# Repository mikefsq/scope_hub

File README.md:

# scope_hub

Telescope power and USB hub: six 12V/4A outputs, six 5 Gbit/s USB-C ports supplying 5V/2A, all ports support
switching, pwm control, and current monitoring. It also has a GPS, environment sensors and a Qwiic 
port. One of the six USB ports supports 5A to power a raspberry pi 5. Controled as a USB-HID device.

| Directory | Contents | License |
|---|---|---|
| `firmware` | RP2350 firmware | AGPL-3.0 |
| `driver` | Go driver and `scopehub` command | AGPL-3.0 |
| `pcb` | KiCad project | CERN-OHL-S-2.0 |
| `mech` | enclosure STEP files | CERN-OHL-S-2.0 |

See also the Alpaca switch driver is `scopehub` in [goalpaca-devices](https://github.com/mikefsq/goalpaca-devices).

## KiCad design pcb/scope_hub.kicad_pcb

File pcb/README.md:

# Scope Hub PCB

KiCad 10 project for the Scope Hub board: an RP2350A controller with six
switched 12 V outputs, six USB-C ports behind two TUSB hubs, per-port current
monitors, a GPS receiver and environment sensors.

- `scope_hub.kicad_pro` opens the project. `scope_hub.kicad_sch` is the root
  schematic; the other `.kicad_sch` files are its sheets.
- `scope_hub.kicad_pcb` is the layout, with custom rules in `scope_hub.kicad_dru`.
- `scope_hub.kicad_sym`, `scope_hub.pretty` and `scope_hub.3dshapes` hold the
  project's own symbols, footprints and 3D models. The library tables point at
  them relative to the project, so the folder opens as is on another machine.
- `fabrication-toolkit-options.json` configures the Fabrication Toolkit plugin,
  which writes the JLCPCB Gerbers, BOM and placement files.

The firmware is in `../firmware` and the host driver in `../driver`.

## License

Copyright (c) 2026 mikefsq

This source describes Open Hardware and is licensed under the CERN-OHL-S v2.
You may redistribute and modify this source and make products using it under
the terms of the [CERN-OHL-S v2](LICENSE). This source is distributed WITHOUT
ANY EXPRESS OR IMPLIED WARRANTY, INCLUDING OF MERCHANTABILITY, SATISFACTORY
QUALITY AND FITNESS FOR A PARTICULAR PURPOSE. Please see the CERN-OHL-S v2
for applicable conditions.

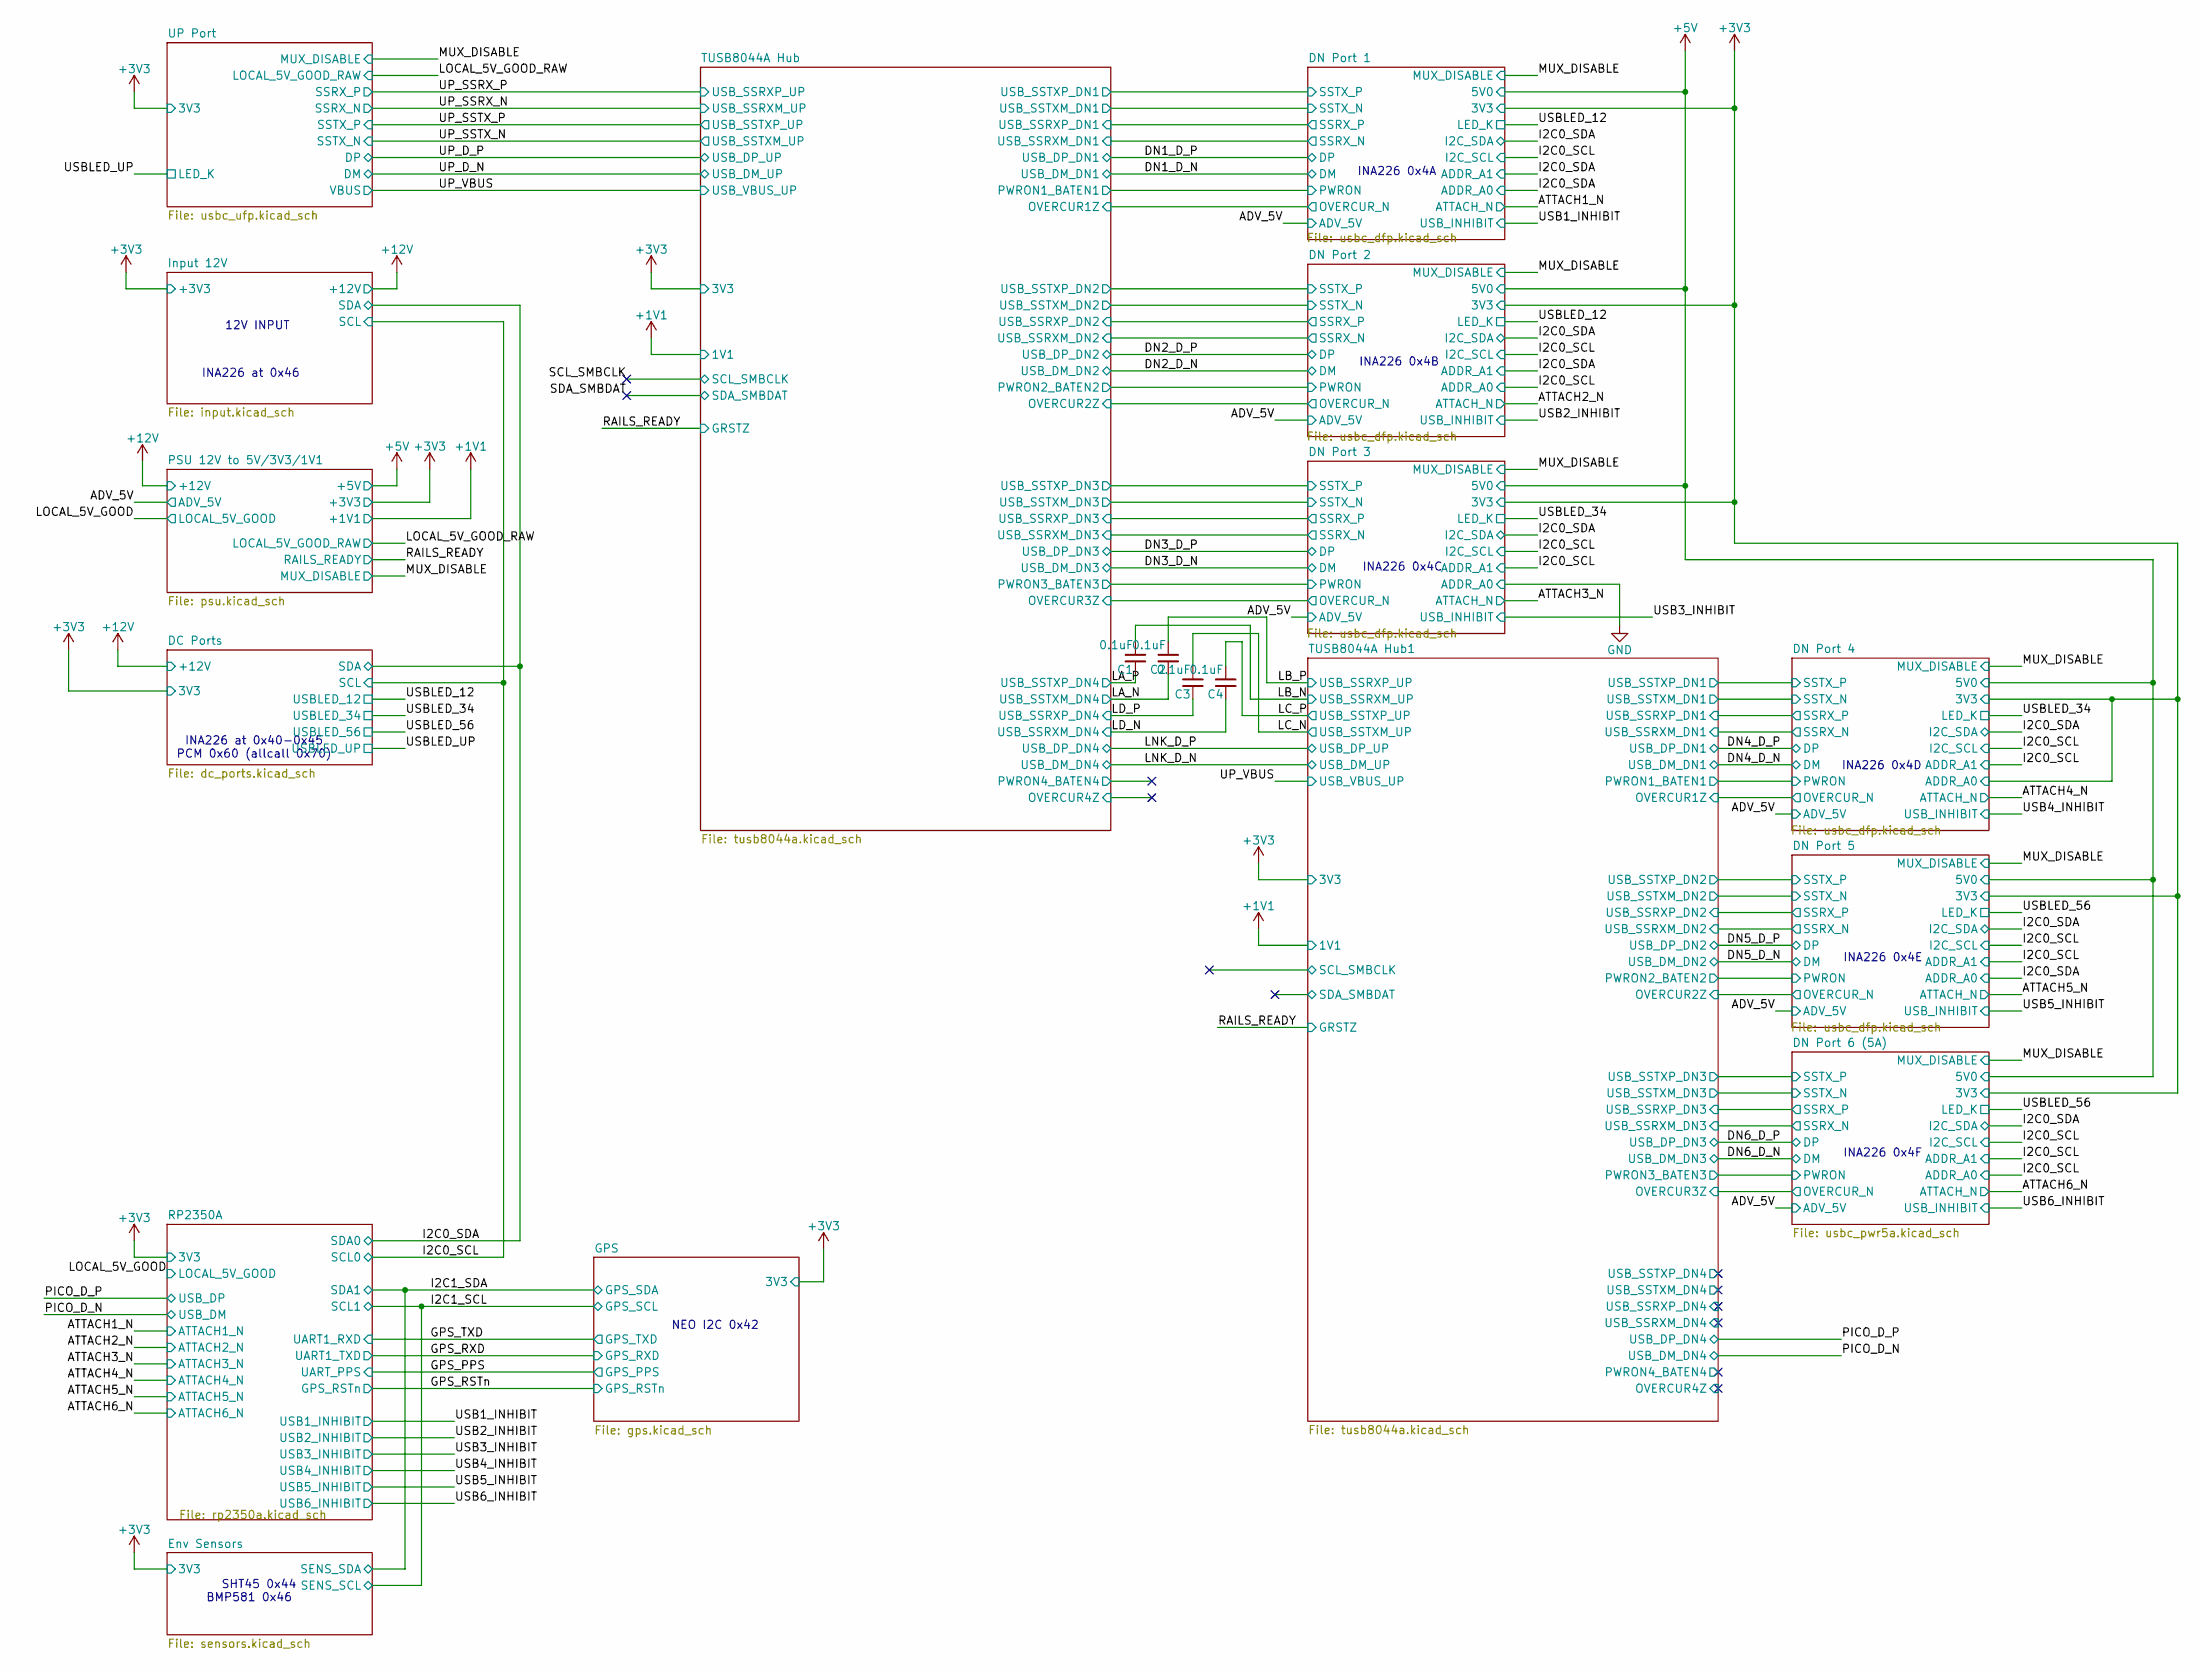
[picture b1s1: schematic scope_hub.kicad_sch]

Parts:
C1, C2, C3, C4: 0.1uF; C_0402_1005Metric; LCSC C1525

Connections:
/LA_N: C2.1; also elsewhere on the board
/LA_P: C1.1; also elsewhere on the board
/LB_N: C1.2; also elsewhere on the board
/LB_P: C2.2; also elsewhere on the board
/LC_N: C3.2; also elsewhere on the board
/LC_P: C4.2; also elsewhere on the board
/LD_N: C4.1; also elsewhere on the board
/LD_P: C3.1; also elsewhere on the board

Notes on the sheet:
12V INPUT
INA226 0x4C
INA226 at 0x40-0x45 PCM 0x60 (allcall 0x70)
INA226 0x4E
INA226 0x4B
INA226 0x4F
INA226 at 0x46
SHT45 0x44
BMP581 0x46
NEO I2C 0x42
INA226 0x4D
INA226 0x4A

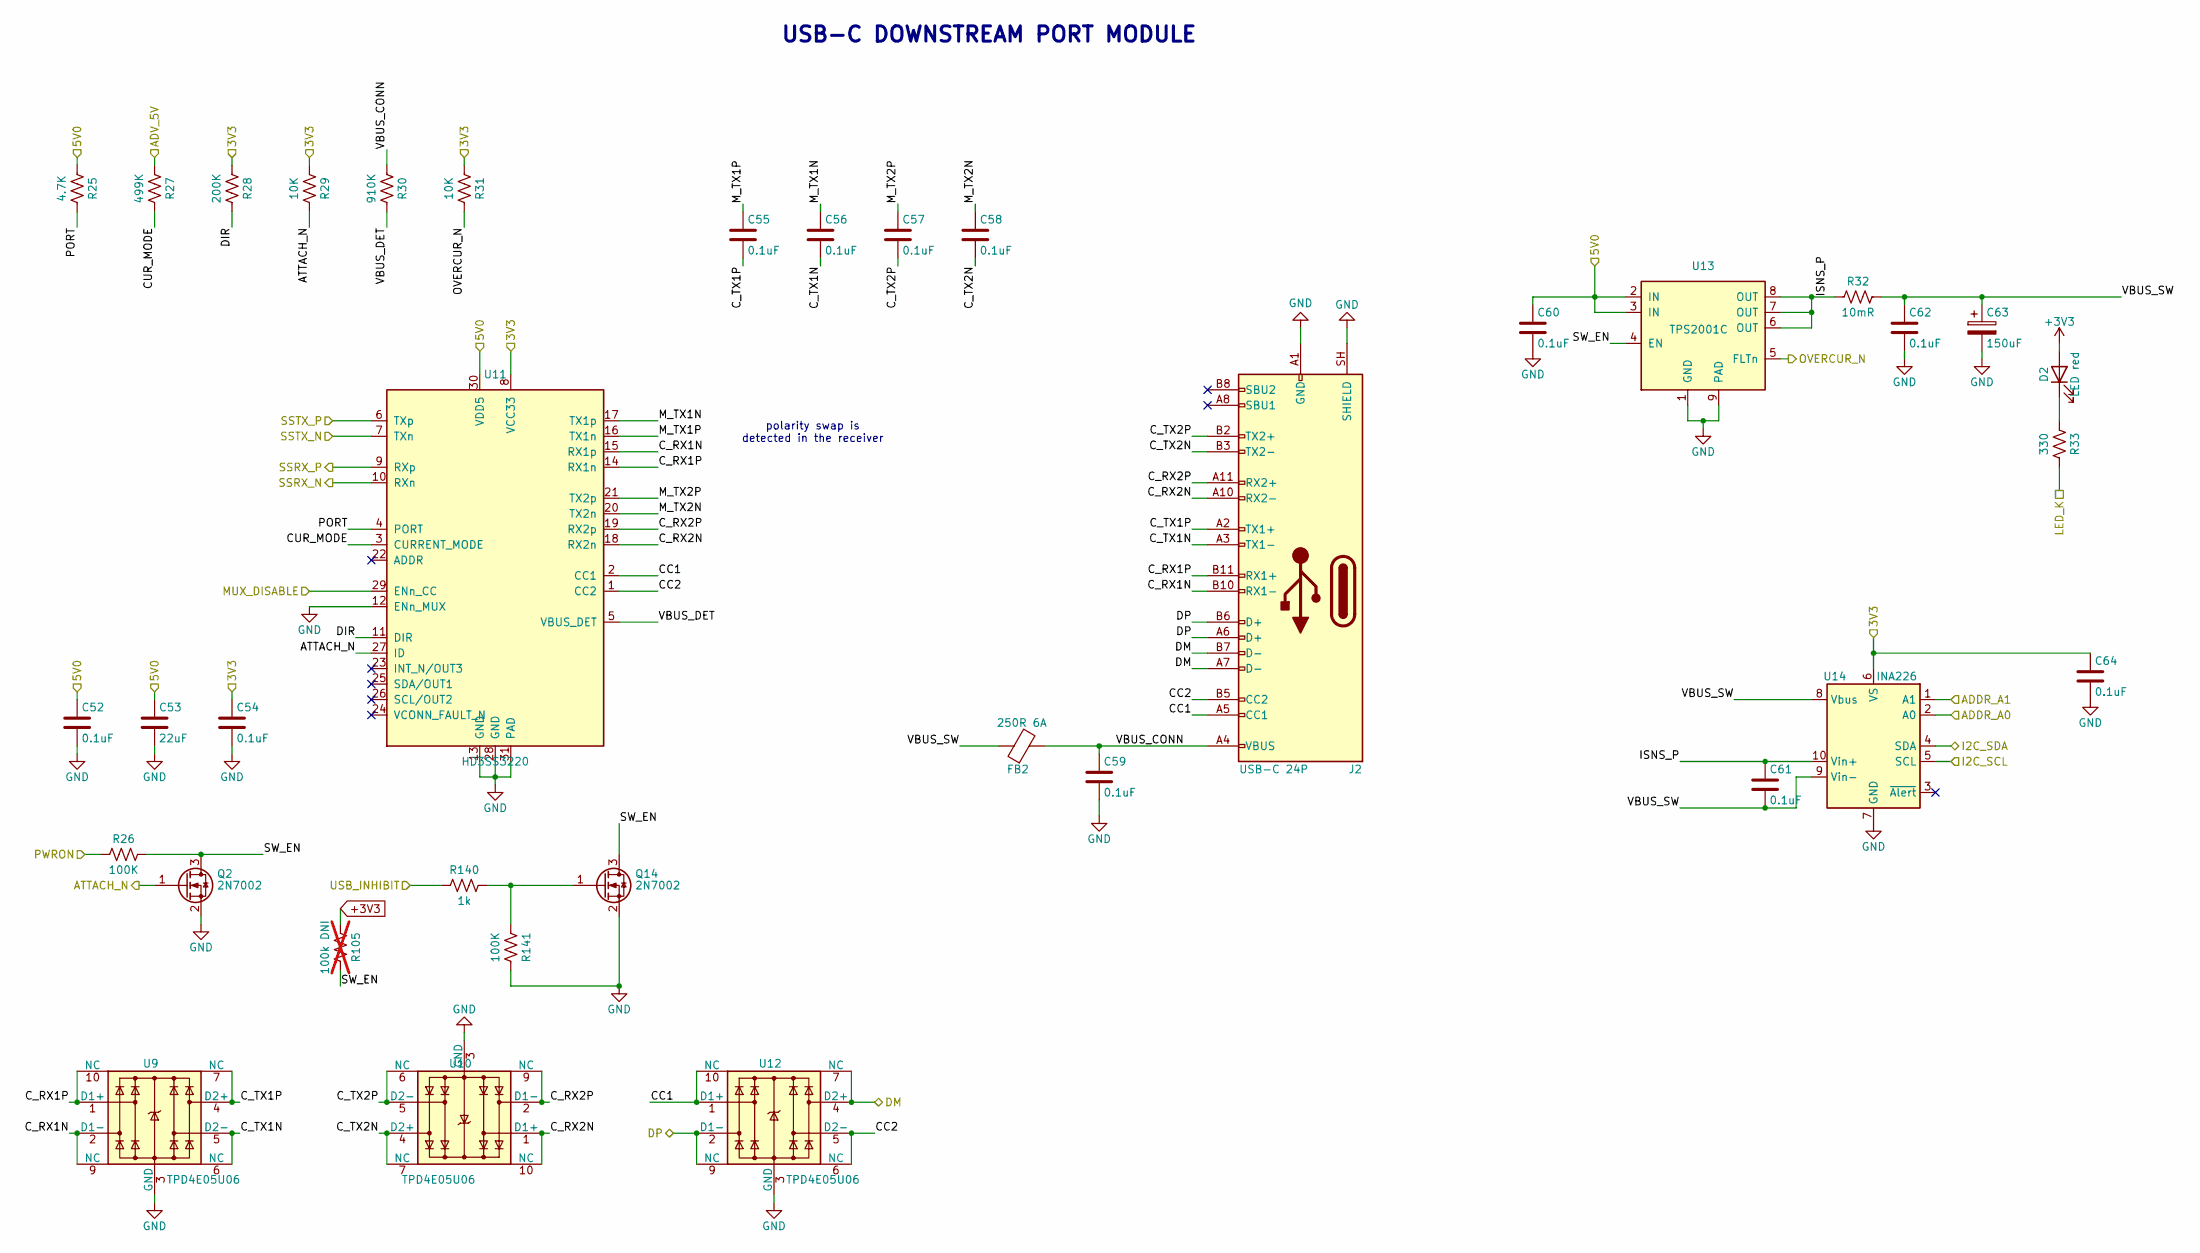
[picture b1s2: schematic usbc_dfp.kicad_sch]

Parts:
C52, C54, C55, C56, C57, C58, C59, C60, C61, C62, C64: 0.1uF; C_0402_1005Metric; LCSC C1525
C53: 22uF; C_0805_2012Metric; LCSC C45783
C63: 150uF; CP_EIA-3528-21_Kemet-B; LCSC C212682
D2: LED red; LED_0805_2012Metric; LCSC C84256
FB2: 250R 6A; FB_201210_PROD; MPN PSBHAA201210H-251T060; LCSC C48543401
J2: USB-C 24P; USB_C_Receptacle_Molex_105450-0101; MPN 105450-0101; LCSC C134092
Q2: 2N7002; SOT-23; LCSC C8545
Q14: 2N7002; SOT-23; MPN 2N7002; LCSC C8545
R25: 4.7K; R_0402_1005Metric; LCSC C25900
R26: 100K; R_0402_1005Metric; LCSC C25741
R27: 499K; R_0402_1005Metric; LCSC C25793
R28: 200K; R_0402_1005Metric; LCSC C25764
R29, R31: 10K; R_0402_1005Metric; LCSC C25744
R30: 910K; R_0402_1005Metric; LCSC C25800
R32: 10mR; R_1206_3216Metric; LCSC C105362
R33: 330; R_0402_1005Metric; LCSC C25104
R105: 100k DNI; R_0402_1005Metric; not fitted
R140: 1k; R_0402_1005Metric; MPN 0402WGF1001TCE; LCSC C11702
R141: 100K; R_0402_1005Metric; MPN 0402WGF1003TCE; LCSC C25741
U9, U10, U12: TPD4E05U06; USON-10_2.5x1.0mm_P0.5mm; LCSC C138714
U11: HD3SS3220; Texas_RNH0030A_WQFN-30-1EP_2.5x4.5mm_P0.4mm_EP1.2x3.2mm; LCSC C165155
U13: TPS2001C; MSOP-8-1EP_3x3mm_P0.65mm_EP1.68x1.88mm; LCSC C473349
U14: INA226; TSSOP-10_3x3mm_P0.5mm; LCSC C49851

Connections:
+3V3: C54.1, C64.1, D2.2 (A), R28.1, R29.1, R31.1, R105.1, U11.8 (VCC33), U14.6 (VS); also elsewhere on the board
+5V: C52.1, C53.1, C60.1, R25.1, U11.30 (VDD5), U13.2 (IN), U13.3 (IN); also elsewhere on the board
/ADV_5V: R27.1; also elsewhere on the board
/ATTACH2_N: Q2.1 (G), R29.2, U11.27 (ID); also elsewhere on the board
/DN2_D_N: J2.A7 (D-), J2.B7 (D-), U12.4 (D2+), U12.7 (NC); also elsewhere on the board
/DN2_D_P: J2.A6 (D+), J2.B6 (D+), U12.2 (D1-), U12.9 (NC); also elsewhere on the board
/DN Port 2/CC1: J2.A5 (CC1), U11.2 (CC1), U12.1 (D1+), U12.10 (NC)
/DN Port 2/CC2: J2.B5 (CC2), U11.1 (CC2), U12.5 (D2-), U12.6 (NC)
/DN Port 2/CUR_MODE: R27.2, U11.3 (CURRENT_MODE)
/DN Port 2/C_RX1N: J2.B10 (RX1-), U9.2 (D1-), U9.9 (NC), U11.15 (RX1p)
/DN Port 2/C_RX1P: J2.B11 (RX1+), U9.1 (D1+), U9.10 (NC), U11.14 (RX1n)
/DN Port 2/C_RX2N: J2.A10 (RX2-), U10.1 (D1+), U10.10 (NC), U11.18 (RX2n)
/DN Port 2/C_RX2P: J2.A11 (RX2+), U10.2 (D1-), U10.9 (NC), U11.19 (RX2p)
/DN Port 2/C_TX1N: C56.2, J2.A3 (TX1-), U9.5 (D2-), U9.6 (NC)
/DN Port 2/C_TX1P: C55.2, J2.A2 (TX1+), U9.4 (D2+), U9.7 (NC)
/DN Port 2/C_TX2N: C58.2, J2.B3 (TX2-), U10.4 (D2+), U10.7 (NC)
/DN Port 2/C_TX2P: C57.2, J2.B2 (TX2+), U10.5 (D2-), U10.6 (NC)
/DN Port 2/DIR: R28.2, U11.11 (DIR)
/DN Port 2/ISNS_P: C61.1, R32.1, U13.6 (OUT), U13.7 (OUT), U13.8 (OUT), U14.10 (Vin+)
/DN Port 2/M_TX1N: C56.1, U11.17 (TX1p)
/DN Port 2/M_TX1P: C55.1, U11.16 (TX1n)
/DN Port 2/M_TX2N: C58.1, U11.20 (TX2n)
/DN Port 2/M_TX2P: C57.1, U11.21 (TX2p)
/DN Port 2/OVERCUR_N: R31.2, U13.5 (FLTn); also elsewhere on the board
/DN Port 2/PORT: R25.2, U11.4 (PORT)
/DN Port 2/SSRX_N: U11.10 (RXn); also elsewhere on the board
/DN Port 2/SSRX_P: U11.9 (RXp); also elsewhere on the board
/DN Port 2/SSTX_N: U11.7 (TXn); also elsewhere on the board
/DN Port 2/SSTX_P: U11.6 (TXp); also elsewhere on the board
/DN Port 2/SW_EN: Q2.3 (D), Q14.3 (D), R26.2, R105.2, U13.4 (EN)
/DN Port 2/VBUS_CONN: C59.1, FB2.2, J2.A4 (VBUS), J2.A9 (VBUS), J2.B4 (VBUS), J2.B9 (VBUS), R30.1
/DN Port 2/VBUS_DET: R30.2, U11.5 (VBUS_DET)
/DN Port 2/VBUS_SW: C61.2, C62.1, C63.1, FB2.1, R32.2, U14.8 (Vbus), U14.9 (Vin-)
/I2C0_SCL: U14.2 (A0), U14.5 (SCL); also elsewhere on the board
/I2C0_SDA: U14.1 (A1), U14.4 (SDA); also elsewhere on the board
/MUX_DISABLE: U11.29 (ENn_CC); also elsewhere on the board
/TUSB8044A Hub/PWRON2_BATEN2: R26.1; also elsewhere on the board
/USB2_INHIBIT: R140.1; also elsewhere on the board
/USBLED_12: R33.2; also elsewhere on the board
GND: C52.2, C53.2, C54.2, C59.2, C60.2, C62.2, C63.2, C64.2, J2.A1 (GND), J2.A12 (GND), J2.B1 (GND), J2.B12 (GND), J2.SH (SHIELD), Q2.2 (S), Q14.2 (S), R141.2, U9.3 (GND), U9.8 (GND), U10.3 (GND), U10.8 (GND), U11.12 (ENn_MUX), U11.13 (GND), U11.28 (GND), U11.31 (PAD), U12.3 (GND), U12.8 (GND), U13.1 (GND), U13.9 (PAD), U14.7 (GND); also elsewhere on the board
unnamed: D2.1 (K), R33.1
unnamed: Q14.1 (G), R140.2, R141.1

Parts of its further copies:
C39, C41, C42, C43, C44, C45, C46, C47, C48, C49, C51, C65, C67, C68, C69, C70, C71, C72, C73, C74, C75, C77, C120, C122, C123, C124, C125, C126, C127, C128, C129, C130, C132, C133, C135, C136, C137, C138, C139, C140, C141, C142, C143, C145: 0.1uF; C_0402_1005Metric; LCSC C1525
C40, C66, C121, C134: 22uF; C_0805_2012Metric; LCSC C45783
C50, C76, C131, C144: 150uF; CP_EIA-3528-21_Kemet-B; LCSC C212682
D1, D3, D5, D6: LED red; LED_0805_2012Metric; LCSC C84256
FB1, FB3, FB5, FB6: 250R 6A; FB_201210_PROD; MPN PSBHAA201210H-251T060; LCSC C48543401
J1, J3, J5, J6: USB-C 24P; USB_C_Receptacle_Molex_105450-0101; MPN 105450-0101; LCSC C134092
Q1, Q3, Q4, Q5: 2N7002; SOT-23; LCSC C8545
Q8, Q9, Q10, Q11: 2N7002; SOT-23; MPN 2N7002; LCSC C8545
R16, R34, R62, R71: 4.7K; R_0402_1005Metric; LCSC C25900
R17, R35, R63, R72: 100K; R_0402_1005Metric; LCSC C25741
R18, R36, R64, R73: 499K; R_0402_1005Metric; LCSC C25793
R19, R37, R65, R74: 200K; R_0402_1005Metric; LCSC C25764
R20, R22, R38, R40, R66, R68, R75, R77: 10K; R_0402_1005Metric; LCSC C25744
R21, R39, R67, R76: 910K; R_0402_1005Metric; LCSC C25800
R23, R41, R69, R78: 10mR; R_1206_3216Metric; LCSC C105362
R24, R42, R70, R79: 330; R_0402_1005Metric; LCSC C25104
R142, R144, R146, R148: 1k; R_0402_1005Metric; MPN 0402WGF1001TCE; LCSC C11702
R143, R145, R147, R149: 100K; R_0402_1005Metric; MPN 0402WGF1003TCE; LCSC C25741
R167, R168, R169, R170: 100k DNI; R_0402_1005Metric; not fitted
U3, U4, U6, U15, U16, U18, U28, U29, U31, U34, U35, U37: TPD4E05U06; USON-10_2.5x1.0mm_P0.5mm; LCSC C138714
U5, U17, U30, U36: HD3SS3220; Texas_RNH0030A_WQFN-30-1EP_2.5x4.5mm_P0.4mm_EP1.2x3.2mm; LCSC C165155
U7, U19, U32, U38: TPS2001C; MSOP-8-1EP_3x3mm_P0.65mm_EP1.68x1.88mm; LCSC C473349
U8, U20, U33, U39: INA226; TSSOP-10_3x3mm_P0.5mm; LCSC C49851

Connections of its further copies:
+3V3: C41.1, C51.1, C67.1, C77.1, C122.1, C132.1, C135.1, C145.1, D1.2 (A), D3.2 (A), D5.2 (A), D6.2 (A), R19.1, R20.1, R22.1, R37.1, R38.1, R40.1, R65.1, R66.1, R68.1, R74.1, R75.1, R77.1, R167.1, R168.1, R169.1, R170.1, U5.8 (VCC33), U8.6 (VS), U17.8 (VCC33), U20.6 (VS), U30.8 (VCC33), U33.2 (A0), U33.6 (VS), U36.8 (VCC33), U39.6 (VS); also elsewhere on the board
+5V: C39.1, C40.1, C47.1, C65.1, C66.1, C73.1, C120.1, C121.1, C128.1, C133.1, C134.1, C141.1, R16.1, R34.1, R62.1, R71.1, U5.30 (VDD5), U7.2 (IN), U7.3 (IN), U17.30 (VDD5), U19.2 (IN), U19.3 (IN), U30.30 (VDD5), U32.2 (IN), U32.3 (IN), U36.30 (VDD5), U38.2 (IN), U38.3 (IN); also elsewhere on the board
/ADV_5V: R18.1, R36.1, R64.1, R73.1; also elsewhere on the board
/ATTACH1_N: Q1.1 (G), R20.2, U5.27 (ID); also elsewhere on the board
/ATTACH3_N: Q3.1 (G), R38.2, U17.27 (ID); also elsewhere on the board
/ATTACH4_N: Q4.1 (G), R66.2, U30.27 (ID); also elsewhere on the board
/ATTACH5_N: Q5.1 (G), R75.2, U36.27 (ID); also elsewhere on the board
/DN1_D_N: J1.A7 (D-), J1.B7 (D-), U6.4 (D2+), U6.7 (NC); also elsewhere on the board
/DN1_D_P: J1.A6 (D+), J1.B6 (D+), U6.2 (D1-), U6.9 (NC); also elsewhere on the board
/DN3_D_N: J3.A7 (D-), J3.B7 (D-), U18.4 (D2+), U18.7 (NC); also elsewhere on the board
/DN3_D_P: J3.A6 (D+), J3.B6 (D+), U18.2 (D1-), U18.9 (NC); also elsewhere on the board
/DN4_D_N: J5.A7 (D-), J5.B7 (D-), U31.4 (D2+), U31.7 (NC); also elsewhere on the board
/DN4_D_P: J5.A6 (D+), J5.B6 (D+), U31.2 (D1-), U31.9 (NC); also elsewhere on the board
/DN5_D_N: J6.A7 (D-), J6.B7 (D-), U37.4 (D2+), U37.7 (NC); also elsewhere on the board
/DN5_D_P: J6.A6 (D+), J6.B6 (D+), U37.2 (D1-), U37.9 (NC); also elsewhere on the board
/DN Port 1/CC1: J1.A5 (CC1), U5.2 (CC1), U6.1 (D1+), U6.10 (NC)
/DN Port 1/CC2: J1.B5 (CC2), U5.1 (CC2), U6.5 (D2-), U6.6 (NC)
/DN Port 1/CUR_MODE: R18.2, U5.3 (CURRENT_MODE)
/DN Port 1/C_RX1N: J1.B10 (RX1-), U3.2 (D1-), U3.9 (NC), U5.15 (RX1p)
/DN Port 1/C_RX1P: J1.B11 (RX1+), U3.1 (D1+), U3.10 (NC), U5.14 (RX1n)
/DN Port 1/C_RX2N: J1.A10 (RX2-), U4.1 (D1+), U4.10 (NC), U5.18 (RX2n)
/DN Port 1/C_RX2P: J1.A11 (RX2+), U4.2 (D1-), U4.9 (NC), U5.19 (RX2p)
/DN Port 1/C_TX1N: C43.2, J1.A3 (TX1-), U3.5 (D2-), U3.6 (NC)
/DN Port 1/C_TX1P: C42.2, J1.A2 (TX1+), U3.4 (D2+), U3.7 (NC)
/DN Port 1/C_TX2N: C45.2, J1.B3 (TX2-), U4.4 (D2+), U4.7 (NC)
/DN Port 1/C_TX2P: C44.2, J1.B2 (TX2+), U4.5 (D2-), U4.6 (NC)
/DN Port 1/DIR: R19.2, U5.11 (DIR)
/DN Port 1/ISNS_P: C48.1, R23.1, U7.6 (OUT), U7.7 (OUT), U7.8 (OUT), U8.10 (Vin+)
/DN Port 1/M_TX1N: C43.1, U5.17 (TX1p)
/DN Port 1/M_TX1P: C42.1, U5.16 (TX1n)
/DN Port 1/M_TX2N: C45.1, U5.20 (TX2n)
/DN Port 1/M_TX2P: C44.1, U5.21 (TX2p)
/DN Port 1/OVERCUR_N: R22.2, U7.5 (FLTn); also elsewhere on the board
/DN Port 1/PORT: R16.2, U5.4 (PORT)
/DN Port 1/SSRX_N: U5.10 (RXn); also elsewhere on the board
/DN Port 1/SSRX_P: U5.9 (RXp); also elsewhere on the board
/DN Port 1/SSTX_N: U5.7 (TXn); also elsewhere on the board
/DN Port 1/SSTX_P: U5.6 (TXp); also elsewhere on the board
/DN Port 1/SW_EN: Q1.3 (D), Q10.3 (D), R17.2, R169.2, U7.4 (EN)
/DN Port 1/VBUS_CONN: C46.1, FB1.2, J1.A4 (VBUS), J1.A9 (VBUS), J1.B4 (VBUS), J1.B9 (VBUS), R21.1
/DN Port 1/VBUS_DET: R21.2, U5.5 (VBUS_DET)
/DN Port 1/VBUS_SW: C48.2, C49.1, C50.1, FB1.1, R23.2, U8.8 (Vbus), U8.9 (Vin-)
/DN Port 3/CC1: J3.A5 (CC1), U17.2 (CC1), U18.1 (D1+), U18.10 (NC)
/DN Port 3/CC2: J3.B5 (CC2), U17.1 (CC2), U18.5 (D2-), U18.6 (NC)
/DN Port 3/CUR_MODE: R36.2, U17.3 (CURRENT_MODE)
/DN Port 3/C_RX1N: J3.B10 (RX1-), U15.2 (D1-), U15.9 (NC), U17.15 (RX1p)
/DN Port 3/C_RX1P: J3.B11 (RX1+), U15.1 (D1+), U15.10 (NC), U17.14 (RX1n)
/DN Port 3/C_RX2N: J3.A10 (RX2-), U16.1 (D1+), U16.10 (NC), U17.18 (RX2n)
/DN Port 3/C_RX2P: J3.A11 (RX2+), U16.2 (D1-), U16.9 (NC), U17.19 (RX2p)
/DN Port 3/C_TX1N: C69.2, J3.A3 (TX1-), U15.5 (D2-), U15.6 (NC)
/DN Port 3/C_TX1P: C68.2, J3.A2 (TX1+), U15.4 (D2+), U15.7 (NC)
/DN Port 3/C_TX2N: C71.2, J3.B3 (TX2-), U16.4 (D2+), U16.7 (NC)
/DN Port 3/C_TX2P: C70.2, J3.B2 (TX2+), U16.5 (D2-), U16.6 (NC)
/DN Port 3/DIR: R37.2, U17.11 (DIR)
/DN Port 3/ISNS_P: C74.1, R41.1, U19.6 (OUT), U19.7 (OUT), U19.8 (OUT), U20.10 (Vin+)
/DN Port 3/M_TX1N: C69.1, U17.17 (TX1p)
/DN Port 3/M_TX1P: C68.1, U17.16 (TX1n)
/DN Port 3/M_TX2N: C71.1, U17.20 (TX2n)
/DN Port 3/M_TX2P: C70.1, U17.21 (TX2p)
/DN Port 3/OVERCUR_N: R40.2, U19.5 (FLTn); also elsewhere on the board
/DN Port 3/PORT: R34.2, U17.4 (PORT)
/DN Port 3/SSRX_N: U17.10 (RXn); also elsewhere on the board
/DN Port 3/SSRX_P: U17.9 (RXp); also elsewhere on the board
/DN Port 3/SSTX_N: U17.7 (TXn); also elsewhere on the board
/DN Port 3/SSTX_P: U17.6 (TXp); also elsewhere on the board
/DN Port 3/SW_EN: Q3.3 (D), Q8.3 (D), R35.2, R167.2, U19.4 (EN)
/DN Port 3/VBUS_CONN: C72.1, FB3.2, J3.A4 (VBUS), J3.A9 (VBUS), J3.B4 (VBUS), J3.B9 (VBUS), R39.1
/DN Port 3/VBUS_DET: R39.2, U17.5 (VBUS_DET)
/DN Port 3/VBUS_SW: C74.2, C75.1, C76.1, FB3.1, R41.2, U20.8 (Vbus), U20.9 (Vin-)
/DN Port 4/CC1: J5.A5 (CC1), U30.2 (CC1), U31.1 (D1+), U31.10 (NC)
/DN Port 4/CC2: J5.B5 (CC2), U30.1 (CC2), U31.5 (D2-), U31.6 (NC)
/DN Port 4/CUR_MODE: R64.2, U30.3 (CURRENT_MODE)
/DN Port 4/C_RX1N: J5.B10 (RX1-), U28.2 (D1-), U28.9 (NC), U30.15 (RX1p)
/DN Port 4/C_RX1P: J5.B11 (RX1+), U28.1 (D1+), U28.10 (NC), U30.14 (RX1n)
/DN Port 4/C_RX2N: J5.A10 (RX2-), U29.1 (D1+), U29.10 (NC), U30.18 (RX2n)
/DN Port 4/C_RX2P: J5.A11 (RX2+), U29.2 (D1-), U29.9 (NC), U30.19 (RX2p)
/DN Port 4/C_TX1N: C124.2, J5.A3 (TX1-), U28.5 (D2-), U28.6 (NC)
/DN Port 4/C_TX1P: C123.2, J5.A2 (TX1+), U28.4 (D2+), U28.7 (NC)
/DN Port 4/C_TX2N: C126.2, J5.B3 (TX2-), U29.4 (D2+), U29.7 (NC)
/DN Port 4/C_TX2P: C125.2, J5.B2 (TX2+), U29.5 (D2-), U29.6 (NC)
/DN Port 4/DIR: R65.2, U30.11 (DIR)
/DN Port 4/ISNS_P: C129.1, R69.1, U32.6 (OUT), U32.7 (OUT), U32.8 (OUT), U33.10 (Vin+)
/DN Port 4/M_TX1N: C124.1, U30.17 (TX1p)
/DN Port 4/M_TX1P: C123.1, U30.16 (TX1n)
/DN Port 4/M_TX2N: C126.1, U30.20 (TX2n)
/DN Port 4/M_TX2P: C125.1, U30.21 (TX2p)
/DN Port 4/OVERCUR_N: R68.2, U32.5 (FLTn); also elsewhere on the board
/DN Port 4/PORT: R62.2, U30.4 (PORT)
/DN Port 4/SSRX_N: U30.10 (RXn); also elsewhere on the board
/DN Port 4/SSRX_P: U30.9 (RXp); also elsewhere on the board
/DN Port 4/SSTX_N: U30.7 (TXn); also elsewhere on the board
/DN Port 4/SSTX_P: U30.6 (TXp); also elsewhere on the board
/DN Port 4/SW_EN: Q4.3 (D), Q9.3 (D), R63.2, R168.2, U32.4 (EN)
/DN Port 4/VBUS_CONN: C127.1, FB5.2, J5.A4 (VBUS), J5.A9 (VBUS), J5.B4 (VBUS), J5.B9 (VBUS), R67.1
/DN Port 4/VBUS_DET: R67.2, U30.5 (VBUS_DET)
/DN Port 4/VBUS_SW: C129.2, C130.1, C131.1, FB5.1, R69.2, U33.8 (Vbus), U33.9 (Vin-)
/DN Port 5/CC1: J6.A5 (CC1), U36.2 (CC1), U37.1 (D1+), U37.10 (NC)
/DN Port 5/CC2: J6.B5 (CC2), U36.1 (CC2), U37.5 (D2-), U37.6 (NC)
/DN Port 5/CUR_MODE: R73.2, U36.3 (CURRENT_MODE)
/DN Port 5/C_RX1N: J6.B10 (RX1-), U34.2 (D1-), U34.9 (NC), U36.15 (RX1p)
/DN Port 5/C_RX1P: J6.B11 (RX1+), U34.1 (D1+), U34.10 (NC), U36.14 (RX1n)
/DN Port 5/C_RX2N: J6.A10 (RX2-), U35.1 (D1+), U35.10 (NC), U36.18 (RX2n)
/DN Port 5/C_RX2P: J6.A11 (RX2+), U35.2 (D1-), U35.9 (NC), U36.19 (RX2p)
/DN Port 5/C_TX1N: C137.2, J6.A3 (TX1-), U34.5 (D2-), U34.6 (NC)
/DN Port 5/C_TX1P: C136.2, J6.A2 (TX1+), U34.4 (D2+), U34.7 (NC)
/DN Port 5/C_TX2N: C139.2, J6.B3 (TX2-), U35.4 (D2+), U35.7 (NC)
/DN Port 5/C_TX2P: C138.2, J6.B2 (TX2+), U35.5 (D2-), U35.6 (NC)
/DN Port 5/DIR: R74.2, U36.11 (DIR)
/DN Port 5/ISNS_P: C142.1, R78.1, U38.6 (OUT), U38.7 (OUT), U38.8 (OUT), U39.10 (Vin+)
/DN Port 5/M_TX1N: C137.1, U36.17 (TX1p)
/DN Port 5/M_TX1P: C136.1, U36.16 (TX1n)
/DN Port 5/M_TX2N: C139.1, U36.20 (TX2n)
/DN Port 5/M_TX2P: C138.1, U36.21 (TX2p)
/DN Port 5/OVERCUR_N: R77.2, U38.5 (FLTn); also elsewhere on the board
/DN Port 5/PORT: R71.2, U36.4 (PORT)
/DN Port 5/SSRX_N: U36.10 (RXn); also elsewhere on the board
/DN Port 5/SSRX_P: U36.9 (RXp); also elsewhere on the board
/DN Port 5/SSTX_N: U36.7 (TXn); also elsewhere on the board
/DN Port 5/SSTX_P: U36.6 (TXp); also elsewhere on the board
/DN Port 5/SW_EN: Q5.3 (D), Q11.3 (D), R72.2, R170.2, U38.4 (EN)
/DN Port 5/VBUS_CONN: C140.1, FB6.2, J6.A4 (VBUS), J6.A9 (VBUS), J6.B4 (VBUS), J6.B9 (VBUS), R76.1
/DN Port 5/VBUS_DET: R76.2, U36.5 (VBUS_DET)
/DN Port 5/VBUS_SW: C142.2, C143.1, C144.1, FB6.1, R78.2, U39.8 (Vbus), U39.9 (Vin-)
/I2C0_SCL: U8.5 (SCL), U20.1 (A1), U20.5 (SCL), U33.1 (A1), U33.5 (SCL), U39.1 (A1), U39.5 (SCL); also elsewhere on the board
/I2C0_SDA: U8.1 (A1), U8.2 (A0), U8.4 (SDA), U20.4 (SDA), U33.4 (SDA), U39.2 (A0), U39.4 (SDA); also elsewhere on the board
/MUX_DISABLE: U5.29 (ENn_CC), U17.29 (ENn_CC), U30.29 (ENn_CC), U36.29 (ENn_CC); also elsewhere on the board
/TUSB8044A Hub1/PWRON1_BATEN1: R63.1; also elsewhere on the board
/TUSB8044A Hub1/PWRON2_BATEN2: R72.1; also elsewhere on the board
/TUSB8044A Hub/PWRON1_BATEN1: R17.1; also elsewhere on the board
/TUSB8044A Hub/PWRON3_BATEN3: R35.1; also elsewhere on the board
/USB1_INHIBIT: R146.1; also elsewhere on the board
/USB3_INHIBIT: R142.1; also elsewhere on the board
/USB4_INHIBIT: R144.1; also elsewhere on the board
/USB5_INHIBIT: R148.1; also elsewhere on the board
/USBLED_12: R24.2; also elsewhere on the board
/USBLED_34: R42.2, R70.2; also elsewhere on the board
/USBLED_56: R79.2; also elsewhere on the board
GND: C39.2, C40.2, C41.2, C46.2, C47.2, C49.2, C50.2, C51.2, C65.2, C66.2, C67.2, C72.2, C73.2, C75.2, C76.2, C77.2, C120.2, C121.2, C122.2, C127.2, C128.2, C130.2, C131.2, C132.2, C133.2, C134.2, C135.2, C140.2, C141.2, C143.2, C144.2, C145.2, J1.A1 (GND), J1.A12 (GND), J1.B1 (GND), J1.B12 (GND), J1.SH (SHIELD), J3.A1 (GND), J3.A12 (GND), J3.B1 (GND), J3.B12 (GND), J3.SH (SHIELD), J5.A1 (GND), J5.A12 (GND), J5.B1 (GND), J5.B12 (GND), J5.SH (SHIELD), J6.A1 (GND), J6.A12 (GND), J6.B1 (GND), J6.B12 (GND), J6.SH (SHIELD), Q1.2 (S), Q3.2 (S), Q4.2 (S), Q5.2 (S), Q8.2 (S), Q9.2 (S), Q10.2 (S), Q11.2 (S), R143.2, R145.2, R147.2, R149.2, U3.3 (GND), U3.8 (GND), U4.3 (GND), U4.8 (GND), U5.12 (ENn_MUX), U5.13 (GND), U5.28 (GND), U5.31 (PAD), U6.3 (GND), U6.8 (GND), U7.1 (GND), U7.9 (PAD), U8.7 (GND), U15.3 (GND), U15.8 (GND), U16.3 (GND), U16.8 (GND), U17.12 (ENn_MUX), U17.13 (GND), U17.28 (GND), U17.31 (PAD), U18.3 (GND), U18.8 (GND), U19.1 (GND), U19.9 (PAD), U20.2 (A0), U20.7 (GND), U28.3 (GND), U28.8 (GND), U29.3 (GND), U29.8 (GND), U30.12 (ENn_MUX), U30.13 (GND), U30.28 (GND), U30.31 (PAD), U31.3 (GND), U31.8 (GND), U32.1 (GND), U32.9 (PAD), U33.7 (GND), U34.3 (GND), U34.8 (GND), U35.3 (GND), U35.8 (GND), U36.12 (ENn_MUX), U36.13 (GND), U36.28 (GND), U36.31 (PAD), U37.3 (GND), U37.8 (GND), U38.1 (GND), U38.9 (PAD), U39.7 (GND); also elsewhere on the board
unnamed: D1.1 (K), R24.1
unnamed: D3.1 (K), R42.1
unnamed: D5.1 (K), R70.1
unnamed: D6.1 (K), R79.1
unnamed: Q8.1 (G), R142.2, R143.1
unnamed: Q9.1 (G), R144.2, R145.1
unnamed: Q10.1 (G), R146.2, R147.1
unnamed: Q11.1 (G), R148.2, R149.1

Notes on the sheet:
USB-C DOWNSTREAM PORT MODULE
polarity swap is detected in the receiver

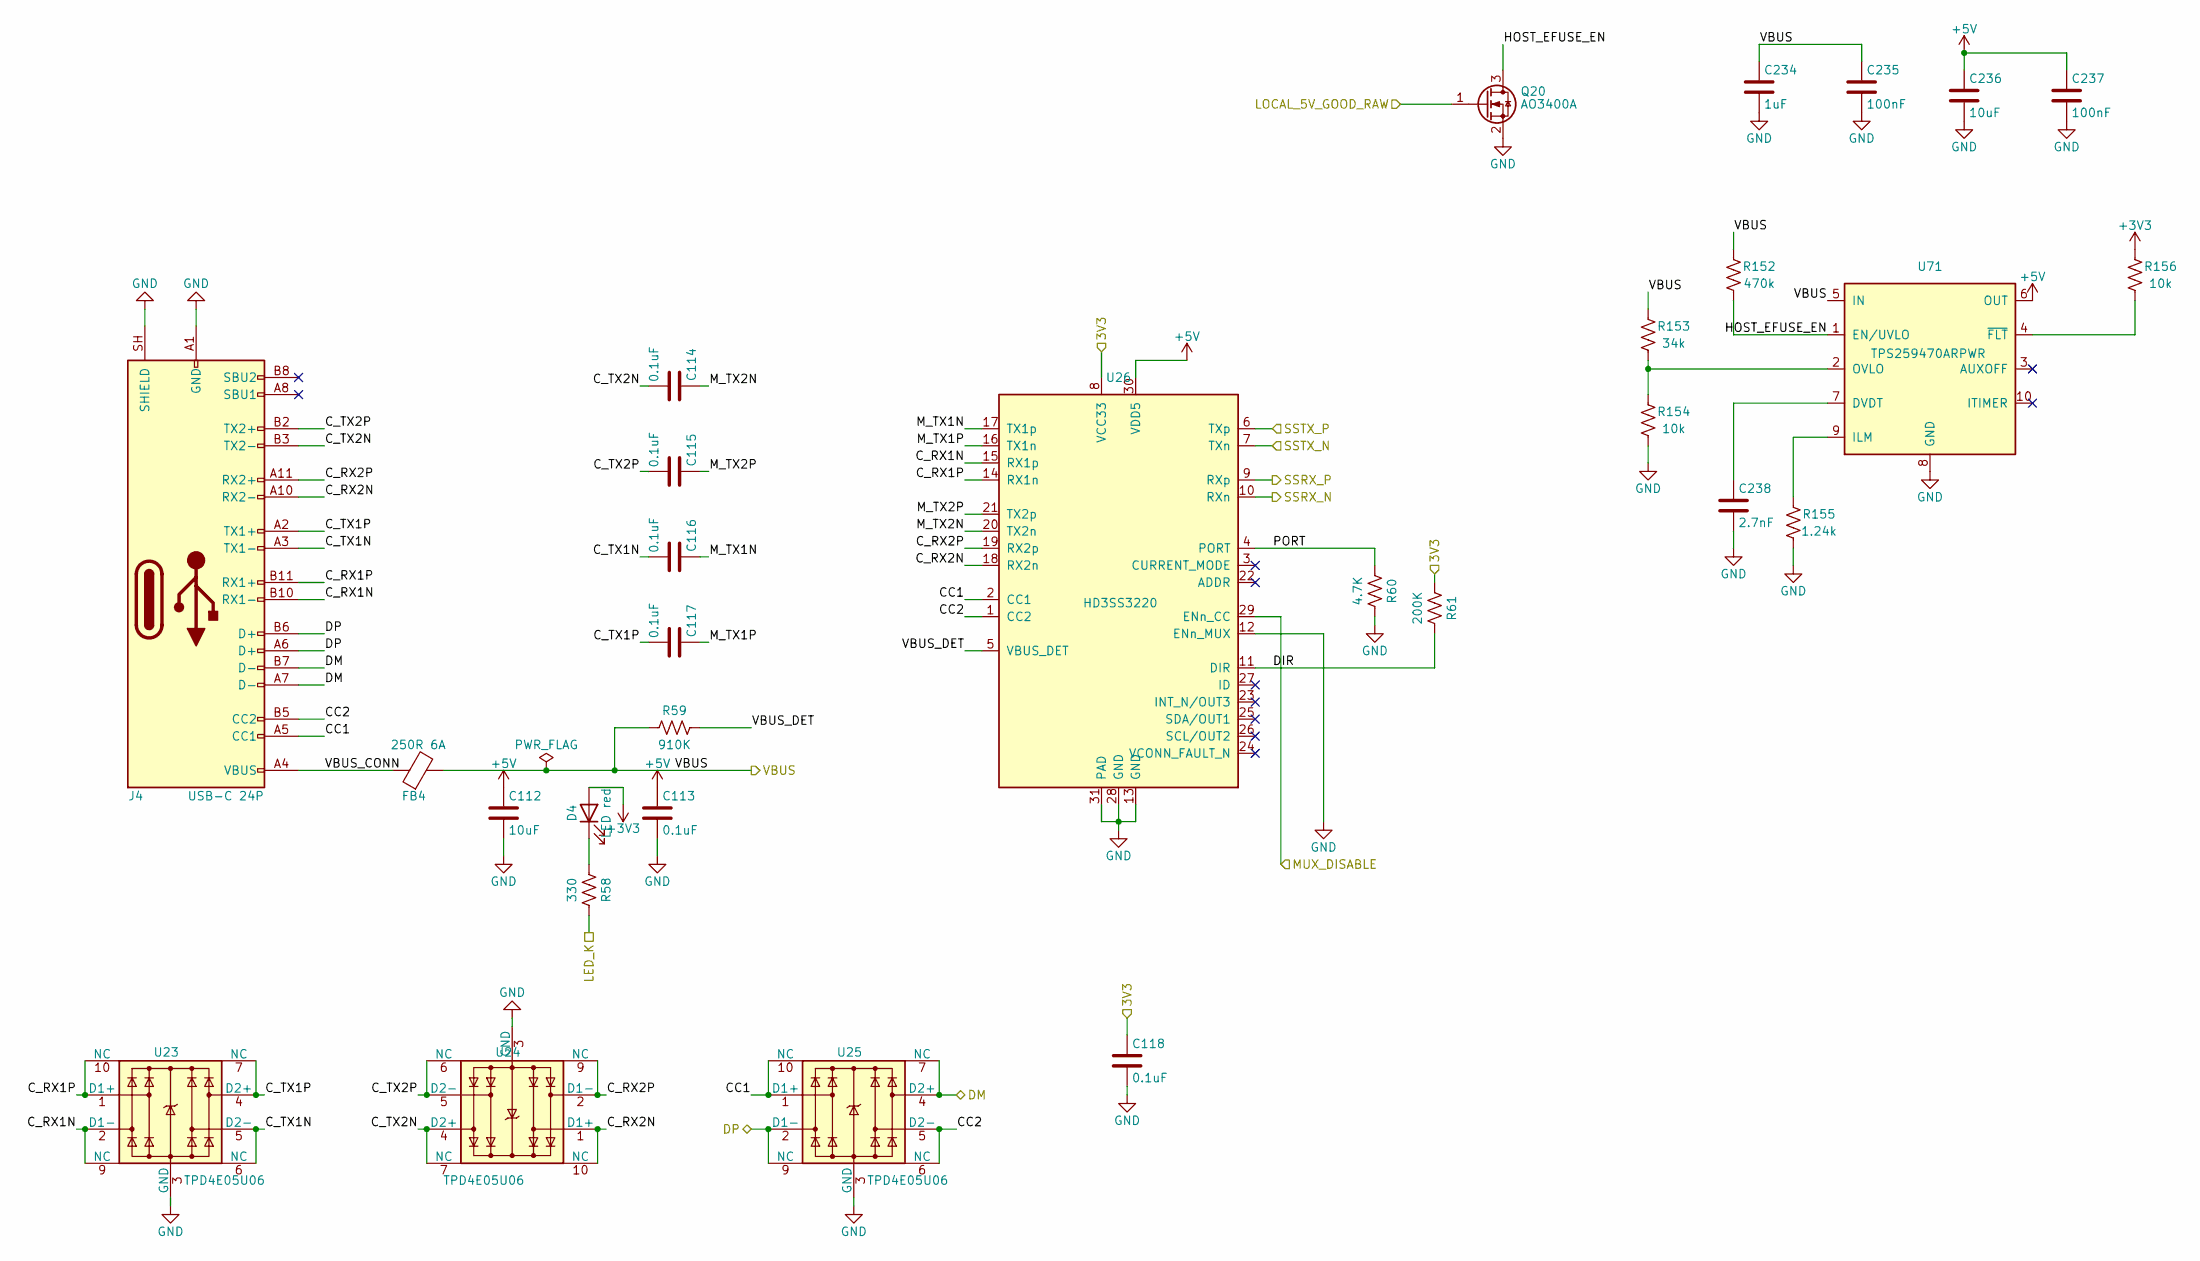
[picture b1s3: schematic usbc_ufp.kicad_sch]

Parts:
C112: 10uF; C_0805_2012Metric; LCSC C15850
C113, C114, C115, C116, C117, C118: 0.1uF; C_0402_1005Metric; LCSC C1525
C234: 1uF; C_0402_1005Metric; Voltage 25V; Tolerance 10%; MPN CL05A105KA5NQNC; LCSC C52923
C235, C237: 100nF; C_0402_1005Metric; Voltage 16V; LCSC C1525
C236: 10uF; C_0805_2012Metric; Voltage 25V; Tolerance 10%; MPN CL21A106KAYNNNE; LCSC C15850
C238: 2.7nF; C_0402_1005Metric; Tolerance 5%; Voltage 50V; MPN GRM1555C1H272JE01D; LCSC C1518205
D4: LED red; LED_0805_2012Metric; LCSC C84256
FB4: 250R 6A; FB_201210_PROD; MPN PSBHAA201210H-251T060; LCSC C48543401
J4: USB-C 24P; USB_C_Receptacle_Molex_105450-0101; MPN 105450-0101; LCSC C134092
Q20: AO3400A; SOT-23; MPN AO3400A; LCSC C20917
R58: 330; R_0402_1005Metric; LCSC C25104
R59: 910K; R_0402_1005Metric; LCSC C25800
R60: 4.7K; R_0402_1005Metric; LCSC C25900
R61: 200K; R_0402_1005Metric; LCSC C25764
R152: 470k; R_0402_1005Metric; Tolerance 1%; MPN 0402WGF4703TCE; LCSC C25790
R153: 34k; R_0402_1005Metric; Tolerance 0.1%; MPN RT0402BRD0734KL; LCSC C852733
R154: 10k; R_0402_1005Metric; Tolerance 0.1%; MPN RT0402BRD0710KL; LCSC C190095
R155: 1.24k; R_0402_1005Metric; Tolerance 1%; MPN 0402WGF1241TCE; LCSC C25864
R156: 10k; R_0402_1005Metric; Tolerance 1%; LCSC C25744
U23, U24, U25: TPD4E05U06; USON-10_2.5x1.0mm_P0.5mm; LCSC C138714
U26: HD3SS3220; Texas_RNH0030A_WQFN-30-1EP_2.5x4.5mm_P0.4mm_EP1.2x3.2mm; LCSC C165155
U71: TPS259470ARPWR; RPW0010A-MFG; MPN TPS259470ARPWR; LCSC C3662799

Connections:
+3V3: C118.1, D4.2 (A), R61.1, R156.1, U26.8 (VCC33); also elsewhere on the board
+5V: C112.1, C113.1, C236.1, C237.1, U26.30 (VDD5), U71.6 (OUT); also elsewhere on the board
/LOCAL_5V_GOOD_RAW: Q20.1 (G); also elsewhere on the board
/MUX_DISABLE: U26.29 (ENn_CC); also elsewhere on the board
/UP Port/CC1: J4.A5 (CC1), U25.1 (D1+), U25.10 (NC), U26.2 (CC1)
/UP Port/CC2: J4.B5 (CC2), U25.5 (D2-), U25.6 (NC), U26.1 (CC2)
/UP Port/C_RX1N: J4.B10 (RX1-), U23.2 (D1-), U23.9 (NC), U26.15 (RX1p)
/UP Port/C_RX1P: J4.B11 (RX1+), U23.1 (D1+), U23.10 (NC), U26.14 (RX1n)
/UP Port/C_RX2N: J4.A10 (RX2-), U24.1 (D1+), U24.10 (NC), U26.18 (RX2n)
/UP Port/C_RX2P: J4.A11 (RX2+), U24.2 (D1-), U24.9 (NC), U26.19 (RX2p)
/UP Port/C_TX1N: C116.2, J4.A3 (TX1-), U23.5 (D2-), U23.6 (NC)
/UP Port/C_TX1P: C117.2, J4.A2 (TX1+), U23.4 (D2+), U23.7 (NC)
/UP Port/C_TX2N: C114.2, J4.B3 (TX2-), U24.4 (D2+), U24.7 (NC)
/UP Port/C_TX2P: C115.2, J4.B2 (TX2+), U24.5 (D2-), U24.6 (NC)
/UP Port/DIR: R61.2, U26.11 (DIR)
/UP Port/HOST_EFUSE_EN: Q20.3 (D), R152.2, U71.1 (EN/UVLO)
/UP Port/M_TX1N: C116.1, U26.17 (TX1p)
/UP Port/M_TX1P: C117.1, U26.16 (TX1n)
/UP Port/M_TX2N: C114.1, U26.20 (TX2n)
/UP Port/M_TX2P: C115.1, U26.21 (TX2p)
/UP Port/PORT: R60.1, U26.4 (PORT)
/UP Port/VBUS_CONN: FB4.1, J4.A4 (VBUS), J4.A9 (VBUS), J4.B4 (VBUS), J4.B9 (VBUS)
/UP Port/VBUS_DET: R59.2, U26.5 (VBUS_DET)
/UP_D_N: J4.A7 (D-), J4.B7 (D-), U25.4 (D2+), U25.7 (NC); also elsewhere on the board
/UP_D_P: J4.A6 (D+), J4.B6 (D+), U25.2 (D1-), U25.9 (NC); also elsewhere on the board
/UP_SSRX_N: U26.10 (RXn); also elsewhere on the board
/UP_SSRX_P: U26.9 (RXp); also elsewhere on the board
/UP_SSTX_N: U26.7 (TXn); also elsewhere on the board
/UP_SSTX_P: U26.6 (TXp); also elsewhere on the board
/UP_VBUS: C234.1, C235.1, FB4.2, R59.1, R152.1, R153.1, U71.5 (IN); also elsewhere on the board
/USBLED_UP: R58.2; also elsewhere on the board
GND: C112.2, C113.2, C118.2, C234.2, C235.2, C236.2, C237.2, C238.2, J4.A1 (GND), J4.A12 (GND), J4.B1 (GND), J4.B12 (GND), J4.SH (SHIELD), Q20.2 (S), R60.2, R154.2, R155.2, U23.3 (GND), U23.8 (GND), U24.3 (GND), U24.8 (GND), U25.3 (GND), U25.8 (GND), U26.12 (ENn_MUX), U26.13 (GND), U26.28 (GND), U26.31 (PAD), U71.8 (GND); also elsewhere on the board
unnamed: D4.1 (K), R58.1
unnamed: C238.1, U71.7 (DVDT)
unnamed: R155.1, U71.9 (ILM)
unnamed: R153.2, R154.1, U71.2 (OVLO)
unnamed: R156.2, U71.4 (~FLT)
